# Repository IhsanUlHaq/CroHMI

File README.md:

# CroHMI
Code for Crop Health Monitoring System using Internet of Things
test

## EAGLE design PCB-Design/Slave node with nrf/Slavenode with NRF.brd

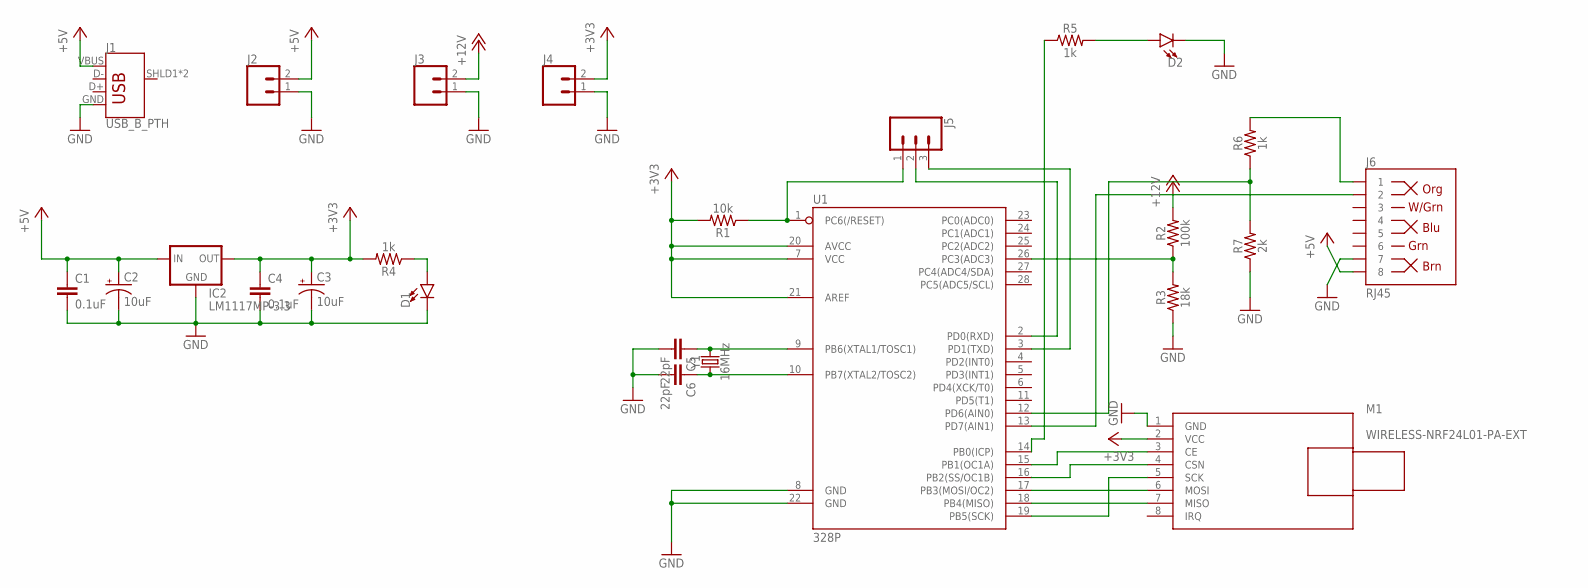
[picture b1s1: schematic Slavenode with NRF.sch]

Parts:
C1, C4: 0.1uF; CAP-PTH-SMALL-KIT
C2, C3: 10uF; CPOL-RADIAL-2.5MM-5MM
C5, C6: 22pF; CAP-PTH-2.54
D1, D2: LED-3MM-NO_SILK; LED_3MM-NS
IC2: LM1117MP-3.3; SOT223
J1: USB_B_PTH; USB-B-PTH
J2, J3, J4: CONN_02; 1X02
J5: CONN_03; 1X03
J6: RJ45; RJ45-8
M1: WIRELESS-NRF24L01-PA-EXT
R1: 10k; AXIAL-0.3
R2: 100k; AXIAL-0.3
R3: 18k; AXIAL-0.3
R4, R5, R6: 1k; AXIAL-0.3
R7: 2k; AXIAL-0.3
U1: 328P; DIP28
Y1: 16MHz; HC49US

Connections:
+3V3: C3.1 (+), C4.1, IC2.2 (OUT), IC2.4 (OUT), J4.2, M1.2 (VCC), R1.P$2 (2), R4.P$2 (2), U1.7 (VCC), U1.20 (AVCC), U1.21 (AREF)
+5V: C1.1, C2.1 (+), IC2.3 (IN), J1.VBUS, J2.2, J6.8
+12V: J3.2, R2.P$2 (2)
GND: C1.2, C2.2 (-), C3.2 (-), C4.2, C5.2, C6.2, D1.K (C), D2.K (C), IC2.1 (GND), J1.GND, J2.1, J3.1, J4.1, J6.7, M1.1 (GND), R3.P$1 (1), R7.P$1 (1), U1.8 (GND), U1.22 (GND)
unnamed: R2.P$1 (1), R3.P$2 (2), U1.26 (PC3(ADC3))
unnamed: D1.A, R4.P$1 (1)
unnamed: J5.1, R1.P$1 (1), U1.1 (PC6(/RESET))
unnamed: M1.6 (MOSI), U1.17 (PB3(MOSI/OC2))
unnamed: M1.7 (MISO), U1.18 (PB4(MISO))
unnamed: C5.1, U1.9 (PB6(XTAL1/TOSC1)), Y1.2
unnamed: C6.1, U1.10 (PB7(XTAL2/TOSC2)), Y1.1
unnamed: J5.2, U1.2 (PD0(RXD))
unnamed: J5.3, U1.3 (PD1(TXD))
unnamed: M1.5 (SCK), U1.19 (PB5(SCK))
unnamed: M1.3 (CE), U1.15 (PB1(OC1A))
unnamed: M1.4 (CSN), U1.16 (PB2(SS/OC1B))
unnamed: J6.2, U1.13 (PD7(AIN1))
unnamed: R6.P$1 (1), R7.P$2 (2), U1.12 (PD6(AIN0))
unnamed: R5.P$1 (1), U1.14 (PB0(ICP))
unnamed: D2.A, R5.P$2 (2)
unnamed: J6.1, R6.P$2 (2)

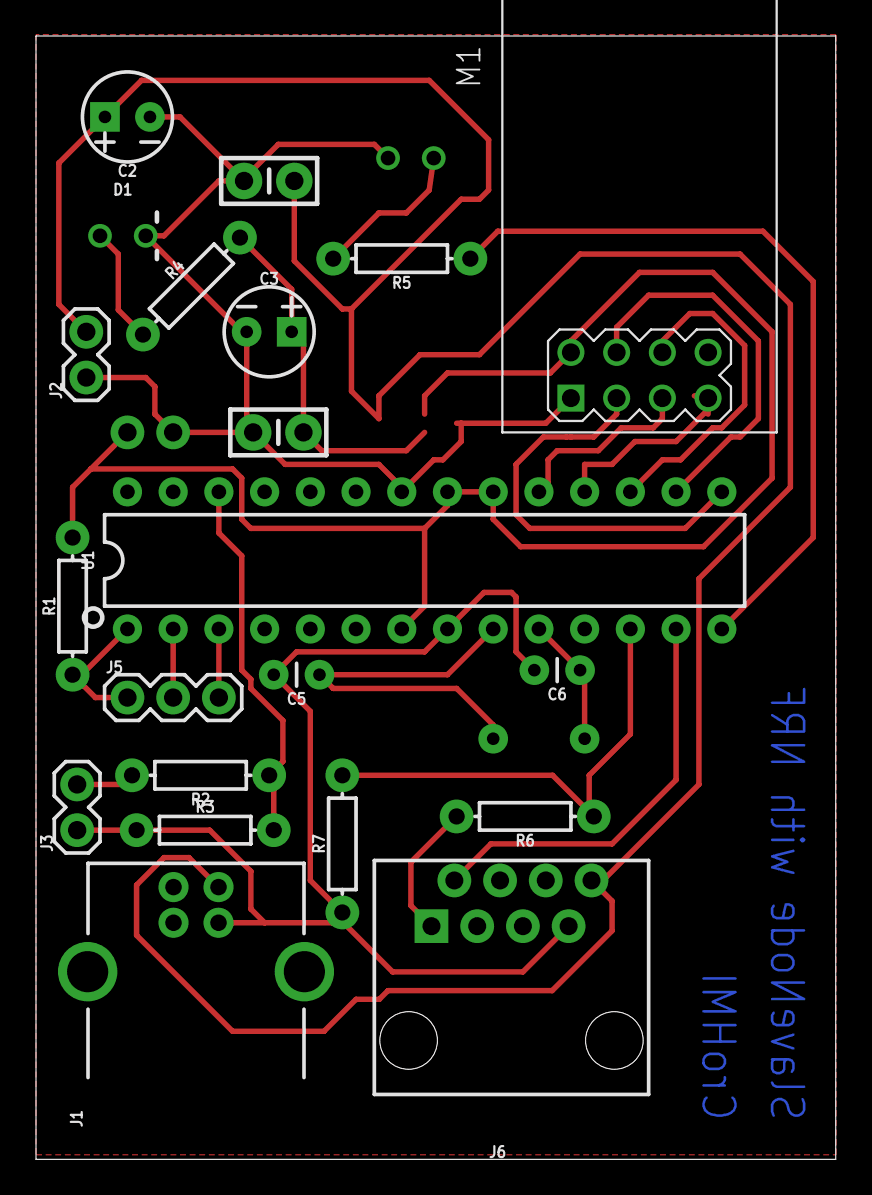
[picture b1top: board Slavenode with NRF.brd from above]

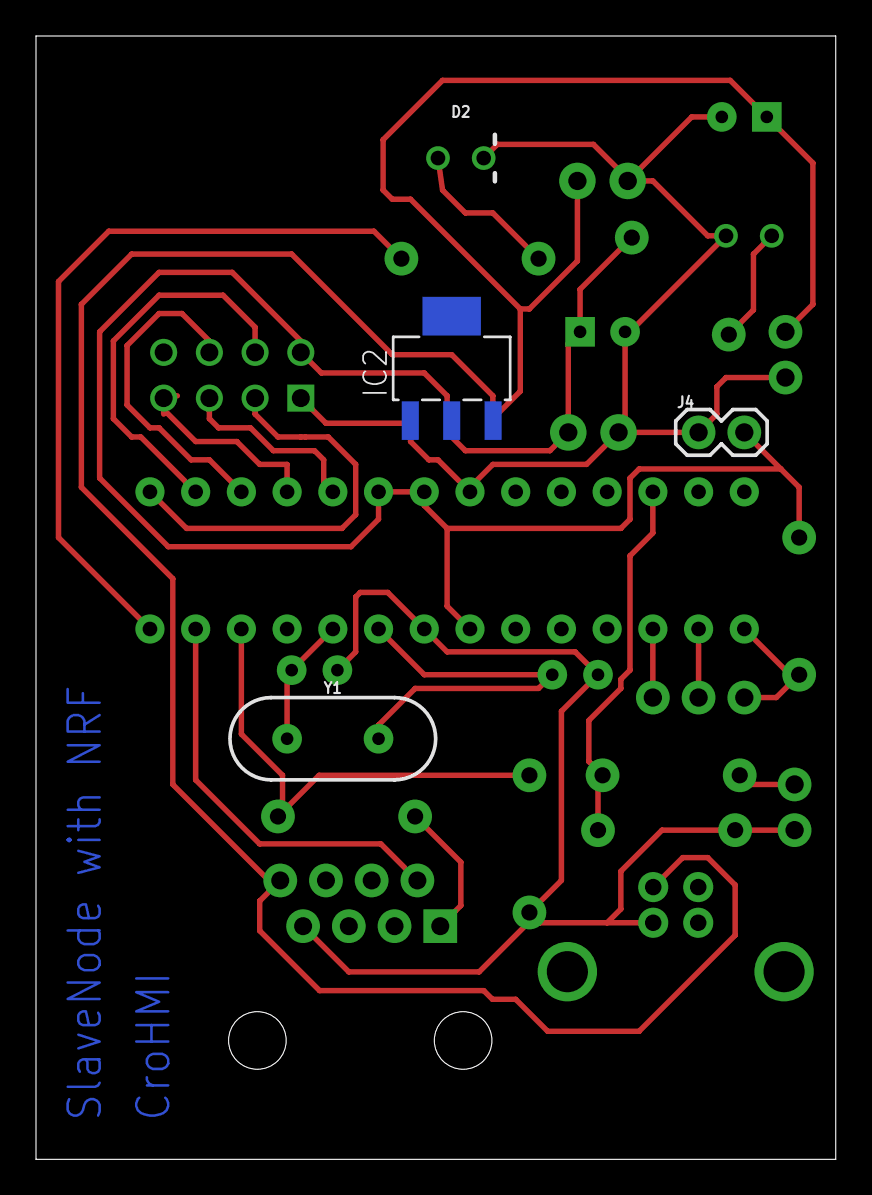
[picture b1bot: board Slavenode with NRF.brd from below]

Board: 2 copper layers, 44.4 x 62.4 mm, 25 parts (4 on the bottom side), 21 nets.

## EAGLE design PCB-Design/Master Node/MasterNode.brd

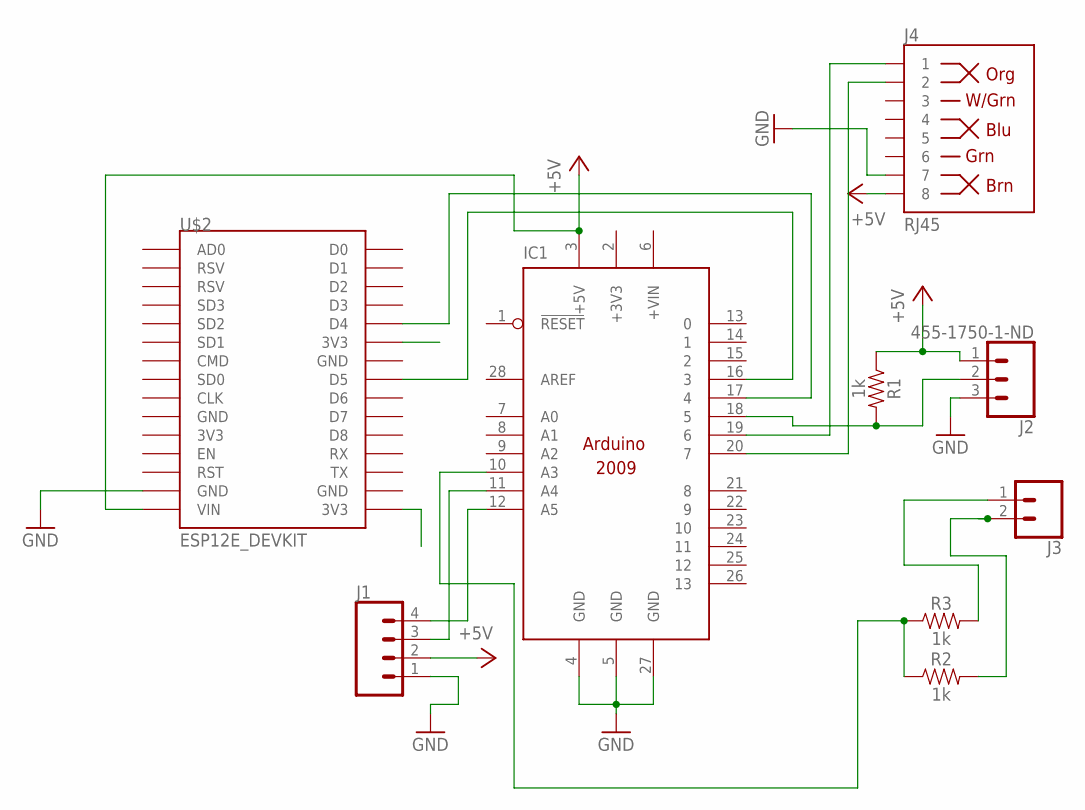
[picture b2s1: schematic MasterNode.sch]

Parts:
IC1: ARDUINO2009_10; ARDUINO2009
J1: CONN_04PTH; 1X04
J2: 455-1750-1-ND; 1X03
J3: CONN_02; 1X02
J4: RJ45; RJ45-8
R1, R2, R3: 1k; AXIAL-0.3
U$2: ESP12E_DEVKIT

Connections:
+3V3: IC1.2 (+3V3)
+5V: IC1.3 (+5V), J1.2, J2.1, J4.8, R1.P$1 (1), U$2.VIN
GND: IC1.4 (GND), IC1.5 (GND), IC1.27 (GND), J1.1, J2.3, J4.7, U$2.GND@1 (GND)
unnamed: IC1.17 (4), U$2.D4
unnamed: IC1.16 (3), U$2.D5
unnamed: IC1.10 (A3), R2.P$1 (1), R3.P$1 (1)
unnamed: IC1.18 (5), J2.2, R1.P$2 (2)
unnamed: IC1.11 (A4), J1.3
unnamed: IC1.12 (A5), J1.4
unnamed: J3.1, R3.P$2 (2)
unnamed: IC1.19 (6), J4.1
unnamed: IC1.20 (7), J4.2
unnamed: J3.2, R2.P$2 (2)

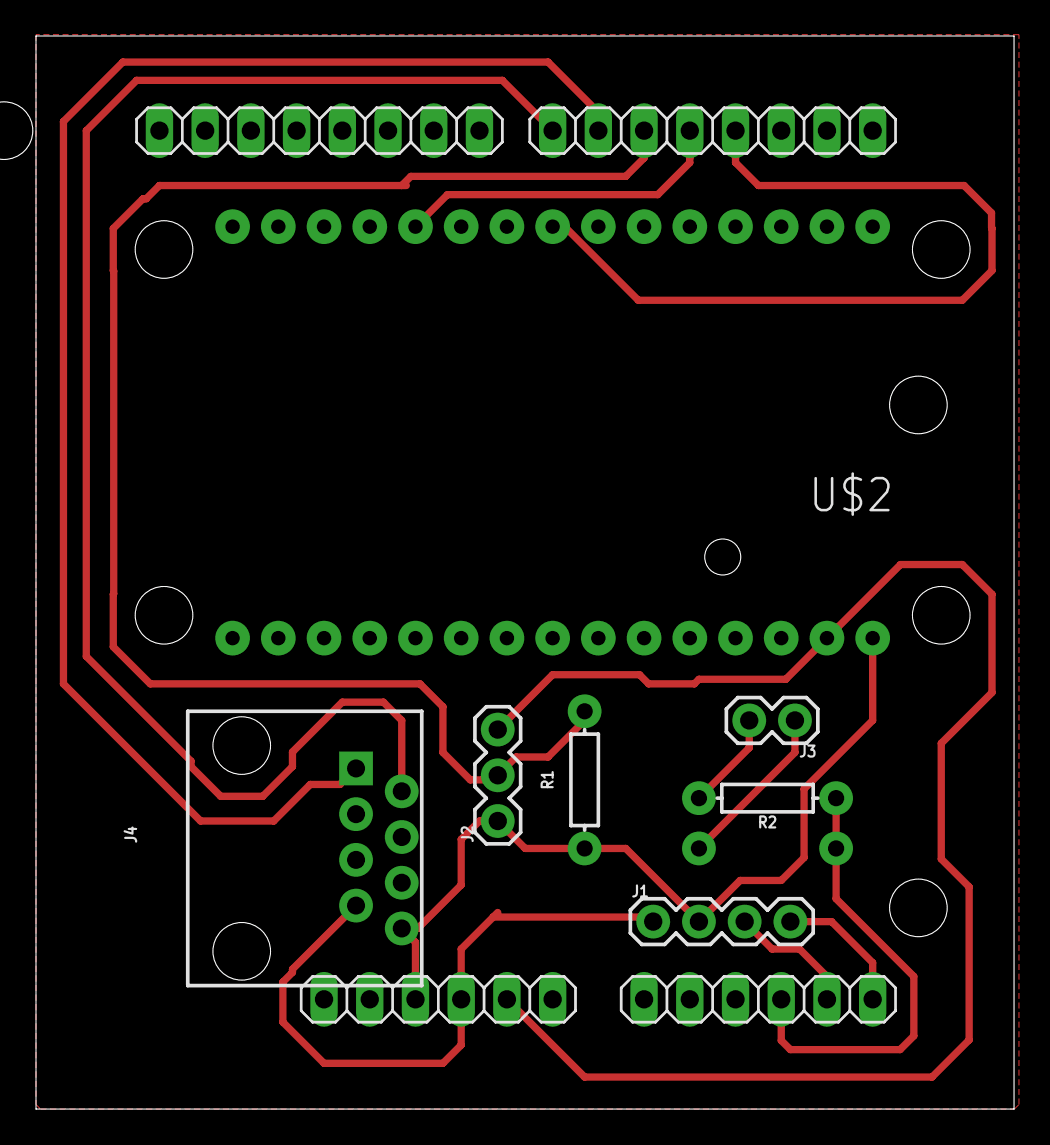
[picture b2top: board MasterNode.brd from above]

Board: 2 copper layers, 54.3 x 59.6 mm, 9 parts (1 on the bottom side), 12 nets.

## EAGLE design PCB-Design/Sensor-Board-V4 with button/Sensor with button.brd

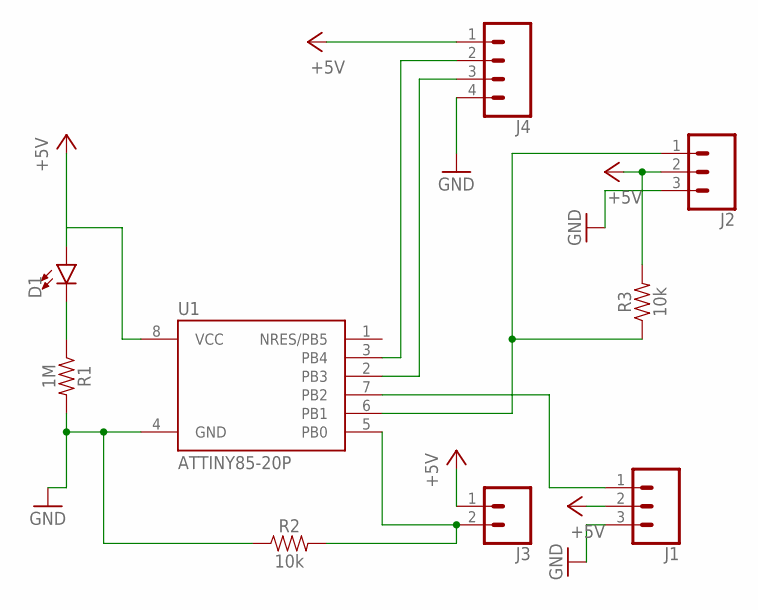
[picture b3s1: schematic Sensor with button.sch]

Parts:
D1: LED3MM; LED_3MM
J1, J2: CONN_03; 1X03
J3: CONN_02; 1X02
J4: CONN_04; 1X04
R1: 1M; AXIAL-0.3
R2, R3: 10k; AXIAL-0.3
U1: ATTINY85-20P; PDIP08_300MIL

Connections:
+5V: D1.A, J1.2, J2.2, J3.1, J4.1, R3.P$2 (2), U1.8 (VCC)
GND: J1.3, J2.3, J4.4, R1.P$2 (2), R2.P$1 (1), U1.4 (GND)
unnamed: D1.K (C), R1.P$1 (1)
unnamed: J4.2, U1.3 (PB4)
unnamed: J1.1, U1.7 (PB2)
unnamed: J2.1, R3.P$1 (1), U1.6 (PB1)
unnamed: J3.2, R2.P$2 (2), U1.5 (PB0)
unnamed: J4.3, U1.2 (PB3)

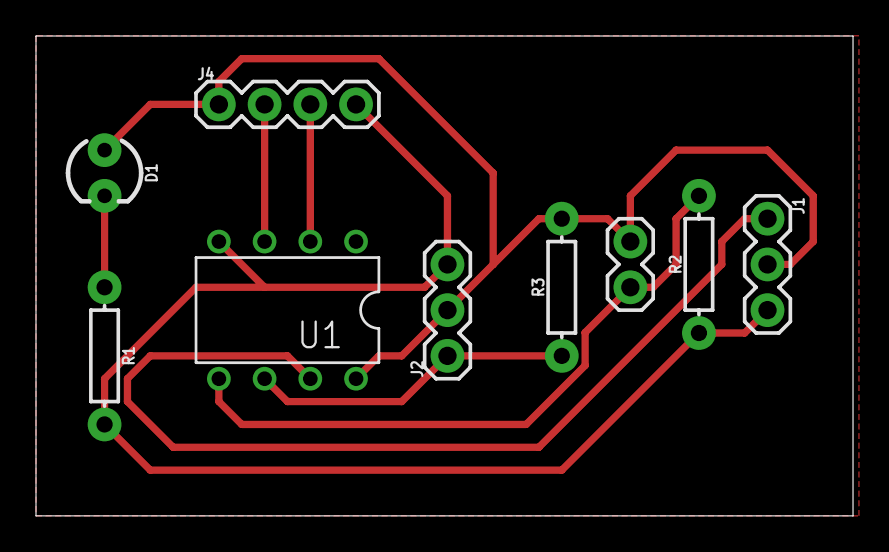
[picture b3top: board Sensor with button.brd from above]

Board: 2 copper layers, 45.4 x 26.7 mm, 9 parts (0 on the bottom side), 8 nets.

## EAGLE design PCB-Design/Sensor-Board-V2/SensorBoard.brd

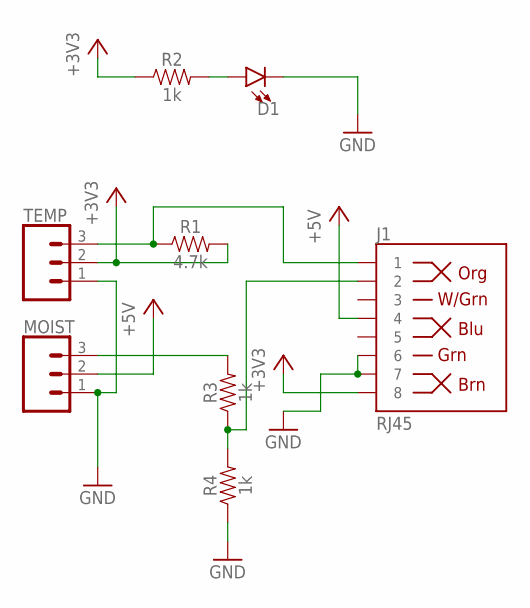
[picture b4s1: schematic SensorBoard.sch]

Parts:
D1: LED3MM; LED_3MM
J1: RJ45; RJ45-8
MOIST: CONN_03; 1X03
R1: 4.7k; AXIAL-0.3
R2, R3, R4: 1k; AXIAL-0.3
TEMP: CONN_03; 1X03

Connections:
+3V3: J1.8, R1.P$2 (2), R2.P$1 (1), TEMP.2
+5V: J1.4, MOIST.2
GND: D1.K (C), J1.6, J1.7, MOIST.1, R4.P$1 (1), TEMP.1
unnamed: J1.2, R3.P$1 (1), R4.P$2 (2)
unnamed: MOIST.3, R3.P$2 (2)
unnamed: D1.A, R2.P$2 (2)
unnamed: J1.1, R1.P$1 (1), TEMP.3

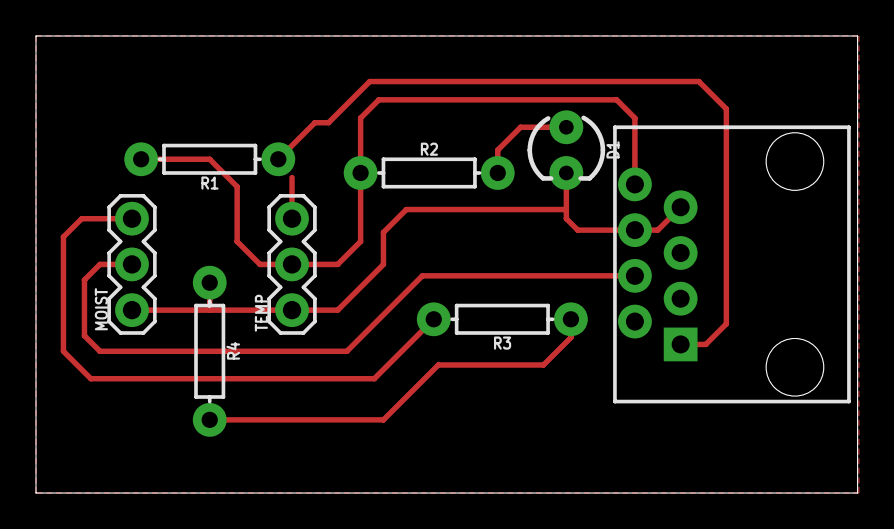
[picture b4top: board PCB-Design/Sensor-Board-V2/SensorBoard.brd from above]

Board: 2 copper layers, 45.6 x 25.4 mm, 8 parts (0 on the bottom side), 7 nets.

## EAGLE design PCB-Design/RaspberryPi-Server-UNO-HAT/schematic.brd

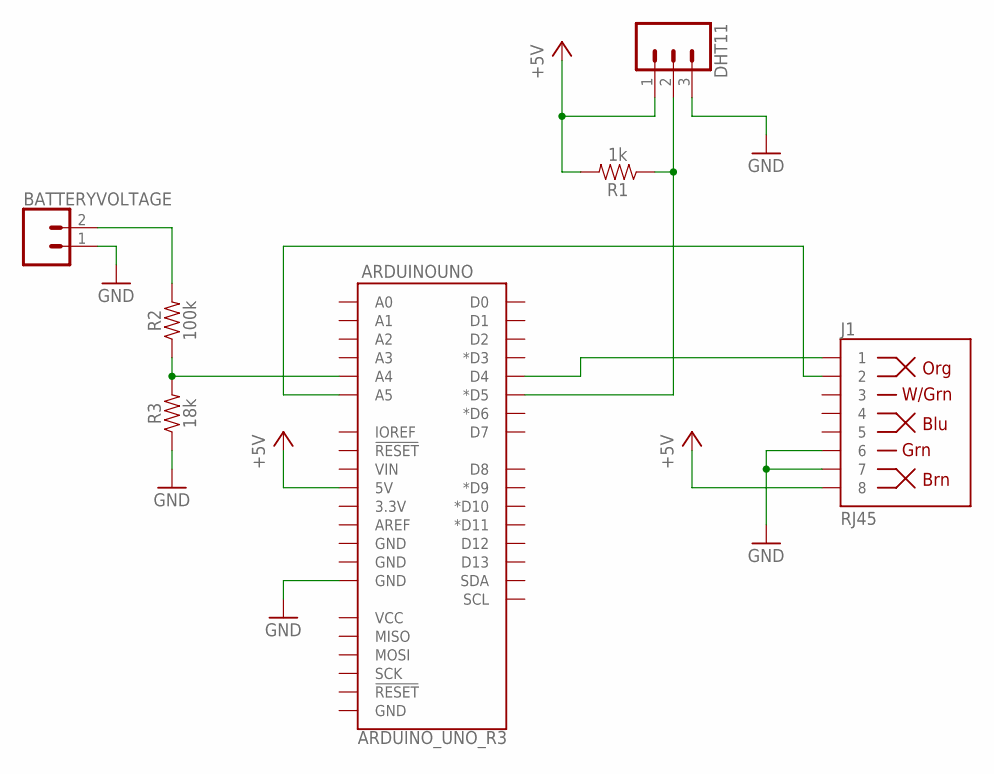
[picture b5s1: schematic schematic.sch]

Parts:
ARDUINOUNO: ARDUINO_UNO_R3; ARDUINO_R3
BATTERYVOLTAGE: CONN_02; 1X02
DHT11: CONN_03; 1X03
J1: RJ45; RJ45-8
R1: 1k; AXIAL-0.3
R2: 100k; AXIAL-0.3
R3: 18k; AXIAL-0.3

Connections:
+5V: ARDUINOUNO.5V, DHT11.1, J1.8, R1.P$2 (2)
GND: ARDUINOUNO.GND@2 (GND), BATTERYVOLTAGE.1, DHT11.3, J1.6, J1.7, R3.P$1 (1)
unnamed: ARDUINOUNO.D4, J1.1
unnamed: ARDUINOUNO.A5, J1.2
unnamed: ARDUINOUNO.A4, R2.P$1 (1), R3.P$2 (2)
unnamed: BATTERYVOLTAGE.2, R2.P$2 (2)
unnamed: ARDUINOUNO.D5 (*D5), DHT11.2, R1.P$1 (1)

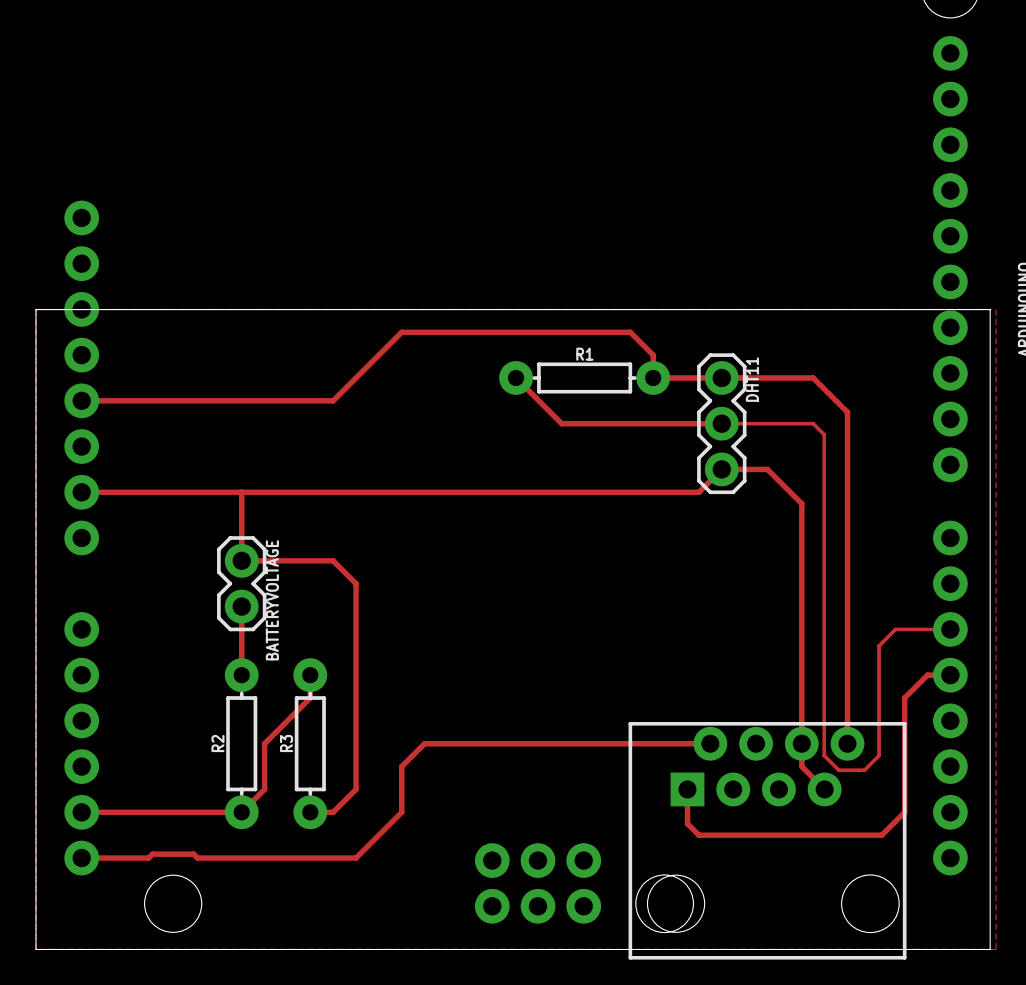
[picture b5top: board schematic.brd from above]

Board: 2 copper layers, 53.0 x 35.6 mm, 7 parts (0 on the bottom side), 7 nets.

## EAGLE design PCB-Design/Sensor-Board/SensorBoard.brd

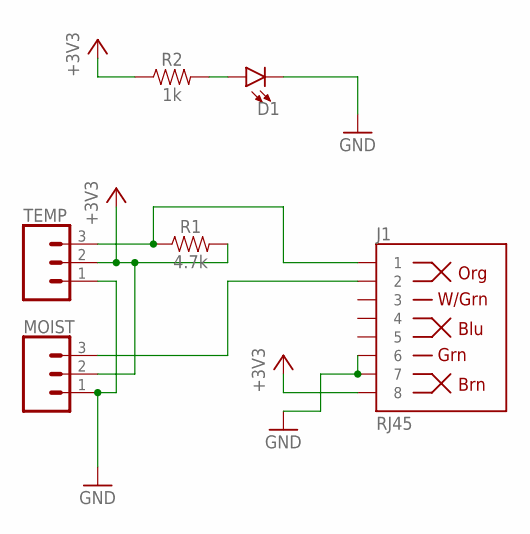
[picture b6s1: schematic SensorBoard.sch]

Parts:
D1: LED3MM; LED_3MM
J1: RJ45; RJ45-8
MOIST: CONN_03; 1X03
R1: 4.7k; AXIAL-0.3
R2: 1k; AXIAL-0.3
TEMP: CONN_03; 1X03

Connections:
+3V3: J1.8, MOIST.2, R1.P$2 (2), R2.P$1 (1), TEMP.2
GND: D1.K (C), J1.6, J1.7, MOIST.1, TEMP.1
unnamed: J1.2, MOIST.3
unnamed: D1.A, R2.P$2 (2)
unnamed: J1.1, R1.P$1 (1), TEMP.3

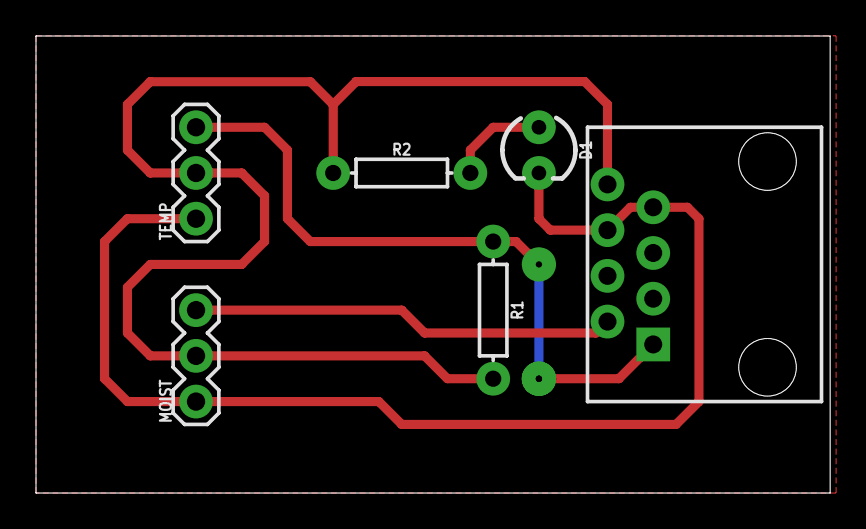
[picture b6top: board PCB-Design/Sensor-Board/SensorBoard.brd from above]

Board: 2 copper layers, 44.1 x 25.4 mm, 6 parts (0 on the bottom side), 5 nets.

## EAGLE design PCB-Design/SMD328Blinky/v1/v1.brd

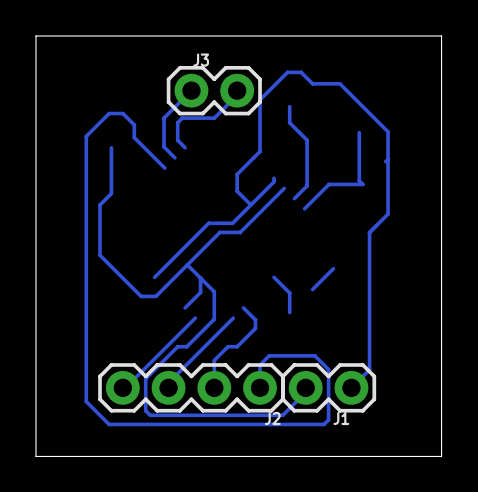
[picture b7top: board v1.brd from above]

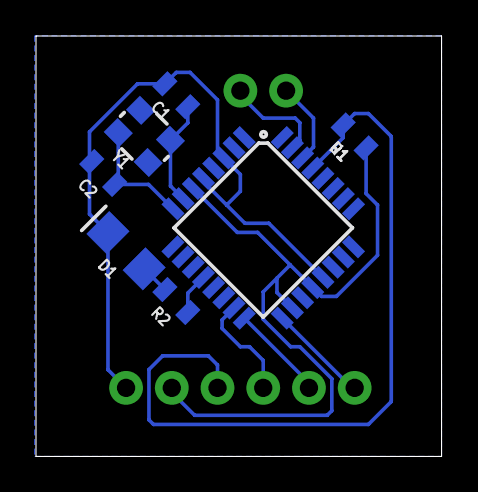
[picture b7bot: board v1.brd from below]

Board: 2 copper layers, 22.5 x 23.4 mm, 10 parts (7 on the bottom side), 12 nets.

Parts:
C1, C2: 22pF; 0805
D1: FKIT-LED-1206
J1, J3: 1X02
J2: 1X04
R1: 10k; 0805
R2: 1k; 0805
U1: ATMEGA328P_TQFP; TQFP32-08
Y1: CRYSTAL-SMD-3.2X2.5MM

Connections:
5V: J1.2, R1.1, U1.4, U1.6, U1.18, U1.20
GND: C1.2, C2.2, D1.C, J1.1, U1.3, U1.5, U1.21
unnamed: C1.1, U1.7, Y1.1
unnamed: C2.1, U1.8, Y1.3
unnamed: J2.1, R1.2, U1.29
unnamed: J2.4, U1.17
unnamed: J2.3, U1.16
unnamed: J2.2, U1.15
unnamed: R2.1, U1.12
unnamed: D1.A, R2.2
unnamed: J3.1, U1.30
unnamed: J3.2, U1.31

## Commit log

2019-02-07 Added the first file
2019-02-07 New Changes
2019-02-07 Adding Misc Files
2019-02-07 Auto Power On for GSM
2019-02-07 Added File for Air Quality GPS Kit
2019-02-07 Changed the resource string
2019-02-07 Updated the resource string
2019-02-08 Addded GPS Functionality
2019-02-08 Changed the name
2019-02-08 Changed the name to MasterNode to avoid confusion
2019-02-08 Completed GPRS Code
2019-02-08 GPS Functionality Added
2019-02-11 Added Watchdog Timer to reset MCU
2019-11-15 Added original files
2019-11-26 Housekeeping
2019-11-26 MacOS BS
2019-11-26 Adding OG Files
2019-11-26 Adding
2019-11-26 MacOS Files
2019-11-29 SMD Blinky PCB
2019-12-06 Deleted useless file
2019-12-12 Changing ArduinoSerialRecieve
2020-01-16 New Master Node
2020-01-23 Crohmi Crud Service
2020-01-28 Change
2020-01-28 mASTER nODE dESIGN
2020-06-28 check
2020-08-31 Last commit
2020-08-31 again
2020-10-08 change in readme
2020-12-08 Add files via upload
    Node 9 added in V4
    New URL implemented and PARAMS changed accordingly in V5
2021-03-26 Add files via upload
    New Crohmi.ml Api added.
    Method changed to post and format is now in jason

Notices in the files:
parts and their libraries:
SparkFun-Connectors: Licensing: Creative Commons ShareAlike 4.0 International - https://creativecommons.org/licenses/by-sa/4.0
diy-modules: Released under the Creative Commons Attribution 4.0 International License: http://creativecommons.org/licenses/by/4.0
